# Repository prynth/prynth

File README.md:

# Prynth
The Prynth framework uses the Raspberry Pi (RPi) for sound synthesis and the Teensy microcontroller for sensor signal acquisition. The Teensy communicates with the RPi through an add-on board, which in turn connects to up to 10 multiplexer boards for a total 80 analog sensor connections (pots, resistors or switches). It also includes connections for digital sensors through I2C and SPI buses.

With the Prynth framework, the RPi boots into a system that automatically runs a web service with a full code editor for the SuperCollider programing language.

For more information please visit the [Prynth website](https://prynth.github.io/).

# Installation

## Prepare the OS

- Flash the latest Raspbian Lite image (https://www.raspberrypi.org/software/operating-systems/#raspberry-pi-os-32-bit) to your microSD card.
- Mount the card on your computer and create an file named ssh located at the root of the boot folder. In Linux:\
`
touch ssh
`
- If you want connect straight to your WiFi, you can also create a wpa_supplicant.conf file on the same booh folder. The wpa_supplicant.conf file should contain:
```
ctrl_interface=DIR=/var/run/wpa_supplicant GROUP=netdev
update_config=1
country=GB
network={
    ssid="your_real_wifi_ssid"
    scan_ssid=1
    psk="your_real_password"
    key_mgmt=WPA-PSK
}
```
- Boot Raspberry Pi.

## Expand filesystem
- SSH to Raspberry Pi and run the Raspbian configuration program.
  - `sudo raspi-config`
- Expand filesystem: "7 Advanced Options" > "A1 Expand Filesystem".
- Reboot.

## Upgrade and install additional libraries
- SSH to Raspberry Pi.
- Update libraries.
  - `sudo apt-get update`
  - `sudo apt-get upgrade`
  - `sudo apt-get dist-upgrade`

- Install additional libraries required for Jack and SuperCollider.
- `sudo apt-get install libsamplerate0-dev libsndfile1-dev libasound2-dev libavahi-client-dev libreadline-dev libfftw3-dev libudev-dev libncurses5-dev cmake git`
- Reboot.

## Compile and install Jack
- `git clone git://github.com/jackaudio/jack2 --depth 1`
- `cd jack2`
- `./waf configure --alsa --libdir=/usr/lib/arm-linux-gnueabihf/`
- `./waf build`
- `sudo ./waf install`
- `sudo ldconfig`
- `cd .. && rm -rf jack2`

## Set limits.conf
- `sudo sh -c "echo @audio - memlock 256000 >> /etc/security/limits.conf"`
- `sudo sh -c "echo @audio - rtprio 75 >> /etc/security/limits.conf"`
- `exit # and ssh in again to make the limits.conf settings work`

## Compile and install Supercollider
- `git clone --recurse-submodules https://github.com/supercollider/supercollider.git`
- `cd supercollider`
- `mkdir build && cd build`
- `cmake -DCMAKE_BUILD_TYPE=Release -DSUPERNOVA=OFF -DSC_ED=OFF -DSC_EL=OFF -DSC_VIM=ON -DNATIVE=ON -DSC_IDE=OFF -DNO_X11=ON -DSC_QT=OFF ..`
- `sudo cmake --build . --config Release --target install`
- `sudo ldconfig`

## Test Jack and SuperCollider
- Connect your soundcard (USB or I2S)
- Run Jack with sound device 1 (-dhw:1)
  - `jackd -P75 -dalsa -dhw:1 -p1024 -n3 -s -r44100 &`
- Run SuperCollider
  - `sclang`
- Inside the sclang shell, boot the server and play an event. You should hear a sound.
  - `s.boot`
  - `(dur:3).play`
- Quit the server and exit sclang
  - `s.quit`
  - `0.exit`

## Setup UART for Prynth boards and enable overclocking
- SSH to Raspberry Pi.
- Run Raspiconfig:
  - `sudo raspi-config`
- Disable shell over serial and enable hardware port:
  - 5 Interfacing Options > P6 Serial
  - "Would you like a login shell to be accessible over serial?" > No
  - "Would you like the serial port hardware to be enabled?" > Yes
- Reboot.
- SSH to Raspberry Pi.
- Additional boot settings (disable Bluetooth and enable overclocking)
  - `sudo sh -c "echo dtoverlay=pi3-disable-bt >> /boot/config.txt"`
## Clone prynth in the pi home folder
- `cd ~`
- `git clone https://github.com/prynth/prynth.git`  

## Install Node.js, liblo and WiringPi
- `sudo apt-get install nodejs liblo7 liblo-dev wiringpi`

## Recompile the pbridge application
- `gcc -o /home/pi/prynth/pbridge/pbridge /home/pi/prynth/pbridge/src/pbridge.c -lwiringPi -llo`

## Enable Prynth at startup
- Launch crontab
  - `crontab -e`
- Choose your preferred text editor (nano is easier)
- Add the following line at the end of the file:
  - `@reboot sudo nodejs /home/pi/prynth/server/bin/www`
- Reboot.

# Notes
For more information please refer to the [Prynth documentation](https://prynth.github.io/doc/). Prynth is also distributed as a ready-to-use image file hosted on the [Downloads](https://prynth.github.io/create/downloads.html) section.

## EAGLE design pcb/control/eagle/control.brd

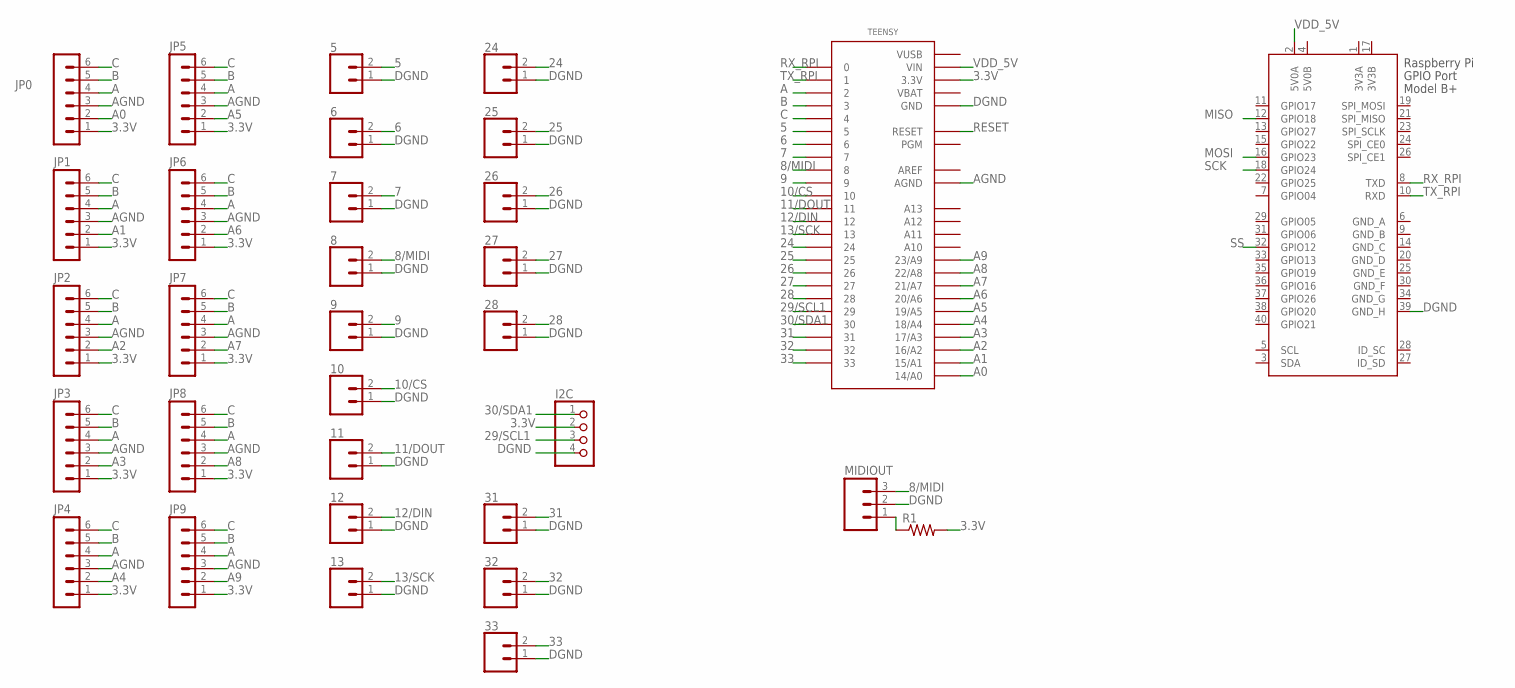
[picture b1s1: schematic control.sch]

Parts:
5, 6, 7, 8, 9, 10, 11, 12, 13, 24, 25, 26, 27, 28, 31, 32, 33: CONN_02; 1X02
I2C: PINHD-1X4; 1X04
JP0, JP1, JP2, JP3, JP4, JP5, JP6, JP7, JP8, JP9: MA06-1
MIDIOUT: M03PTH; 1X03
R1: RESISTORAXIAL-0.3; AXIAL-0.3
TEENSY: TEENSY_3.0_ALLPINS
X1: RASPI_BOARD_B+#_H; RASPI_BOARD_B+HAT

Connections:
3.3V: I2C.2, JP0.1, JP1.1, JP2.1, JP3.1, JP4.1, JP5.1, JP6.1, JP7.1, JP8.1, JP9.1, R1.P$2 (2), TEENSY.3.3V, TEENSY.3.3V1 (3.3V), TEENSY.3.3V2 (3.3V)
3V3A: X1.1 (3V3A)
3V3B: X1.17 (3V3B)
5: 5.2, TEENSY.5
5V0B: X1.4 (5V0B)
6: 6.2, TEENSY.6
7: 7.2, TEENSY.7
8/MIDI: 8.2, MIDIOUT.3, TEENSY.8
9: 9.2, TEENSY.9
10/CS: 10.2, TEENSY.10
11/DOUT: 11.2, TEENSY.11
12/DIN: 12.2, TEENSY.12
13/SCK: 13.2, TEENSY.13
24: 24.2, TEENSY.24
25: 25.2, TEENSY.25
26: 26.2, TEENSY.26
27: 27.2, TEENSY.27
28: 28.2, TEENSY.28
29/SCL1: I2C.3, TEENSY.29
30/SDA1: I2C.1, TEENSY.30
31: 31.2, TEENSY.31
32: 32.2, TEENSY.32
33: 33.2, TEENSY.33
A: JP0.4, JP1.4, JP2.4, JP3.4, JP4.4, JP5.4, JP6.4, JP7.4, JP8.4, JP9.4, TEENSY.2
A0: JP0.2, TEENSY.14/A0
A1: JP1.2, TEENSY.15/A1
A2: JP2.2, TEENSY.16/A2
A3: JP3.2, TEENSY.17/A3
A4: JP4.2, TEENSY.18/A4
A5: JP5.2, TEENSY.19/A5
A6: JP6.2, TEENSY.20/A6
A7: JP7.2, TEENSY.21/A7
A8: JP8.2, TEENSY.22/A8
A9: JP9.2, TEENSY.23/A9
AGND: JP0.3, JP1.3, JP2.3, JP3.3, JP4.3, JP5.3, JP6.3, JP7.3, JP8.3, JP9.3, TEENSY.AGND
AREF: TEENSY.AREF
B: JP0.5, JP1.5, JP2.5, JP3.5, JP4.5, JP5.5, JP6.5, JP7.5, JP8.5, JP9.5, TEENSY.3
C: JP0.6, JP1.6, JP2.6, JP3.6, JP4.6, JP5.6, JP6.6, JP7.6, JP8.6, JP9.6, TEENSY.4
DGND: 5.1, 6.1, 7.1, 8.1, 9.1, 10.1, 11.1, 12.1, 13.1, 24.1, 25.1, 26.1, 27.1, 28.1, 31.1, 32.1, 33.1, I2C.4, MIDIOUT.2, TEENSY.GND, TEENSY.GND1 (GND), TEENSY.GND2 (GND), X1.39 (GND_H)
GND_A: X1.6 (GND_A)
GND_B: X1.9 (GND_B)
GND_C: X1.14 (GND_C)
GND_D: X1.20 (GND_D)
GND_E: X1.25 (GND_E)
GND_F: X1.30 (GND_F)
GND_G: X1.34 (GND_G)
MISO: X1.12 (GPIO18)
MOSI: X1.16 (GPIO23)
unnamed: MIDIOUT.1, R1.P$1 (1)
RESET: TEENSY.RESET
RX_RPI: TEENSY.0, X1.8 (TXD)
SCK: X1.18 (GPIO24)
SS: X1.32 (GPIO12)
TX_RPI: TEENSY.1, X1.10 (RXD)
VBAT: TEENSY.VBAT
VDD_5V: TEENSY.VIN, X1.2 (5V0A)
VUSB: TEENSY.VUSB

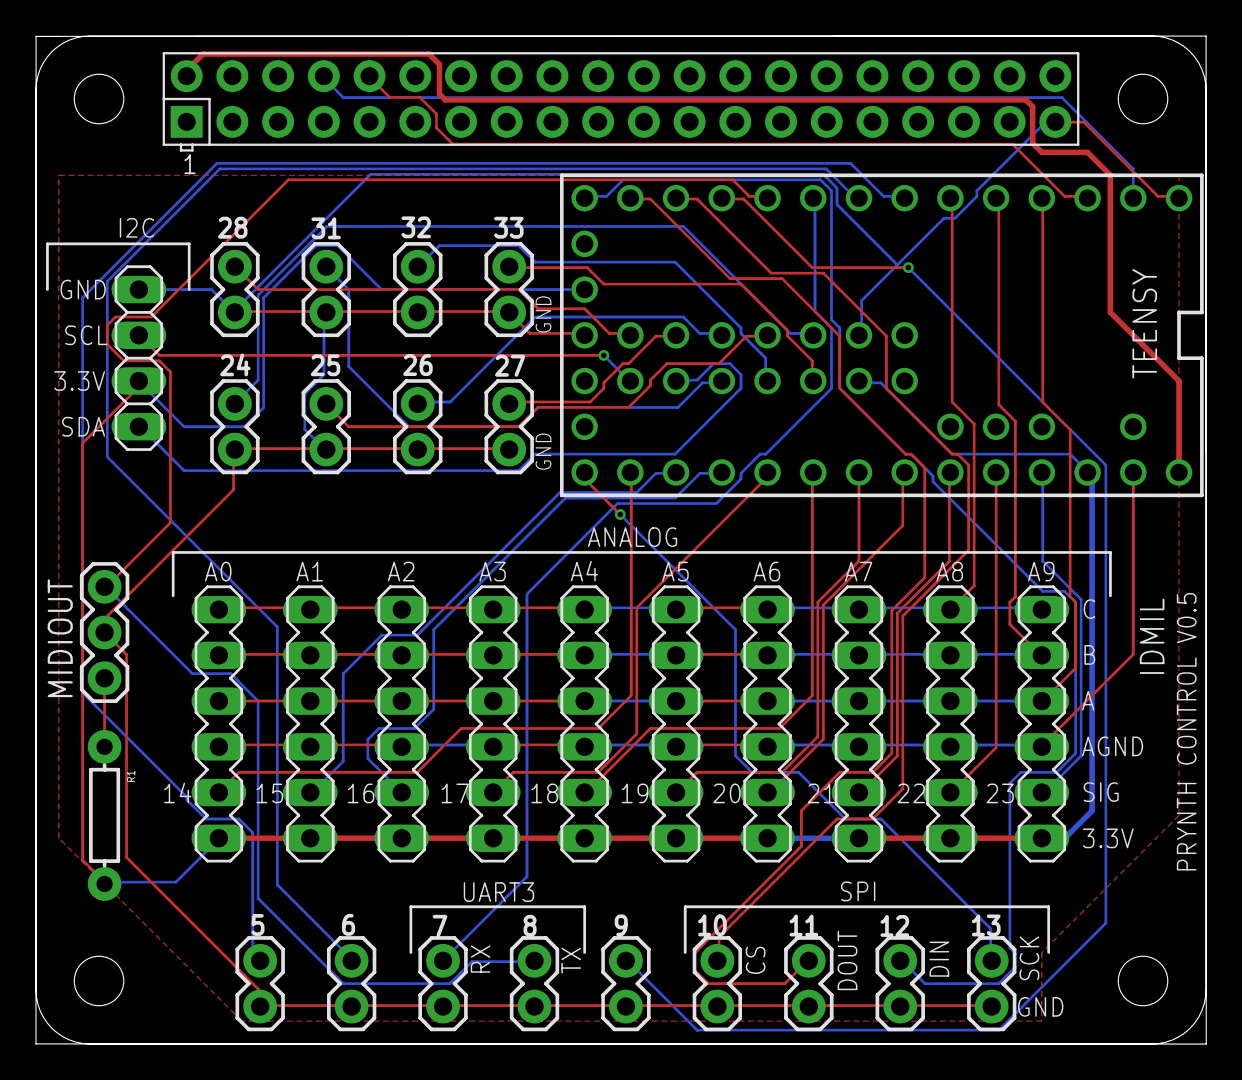
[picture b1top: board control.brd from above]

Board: 2 copper layers, 65.0 x 56.0 mm, 32 parts (0 on the bottom side), 39 nets.

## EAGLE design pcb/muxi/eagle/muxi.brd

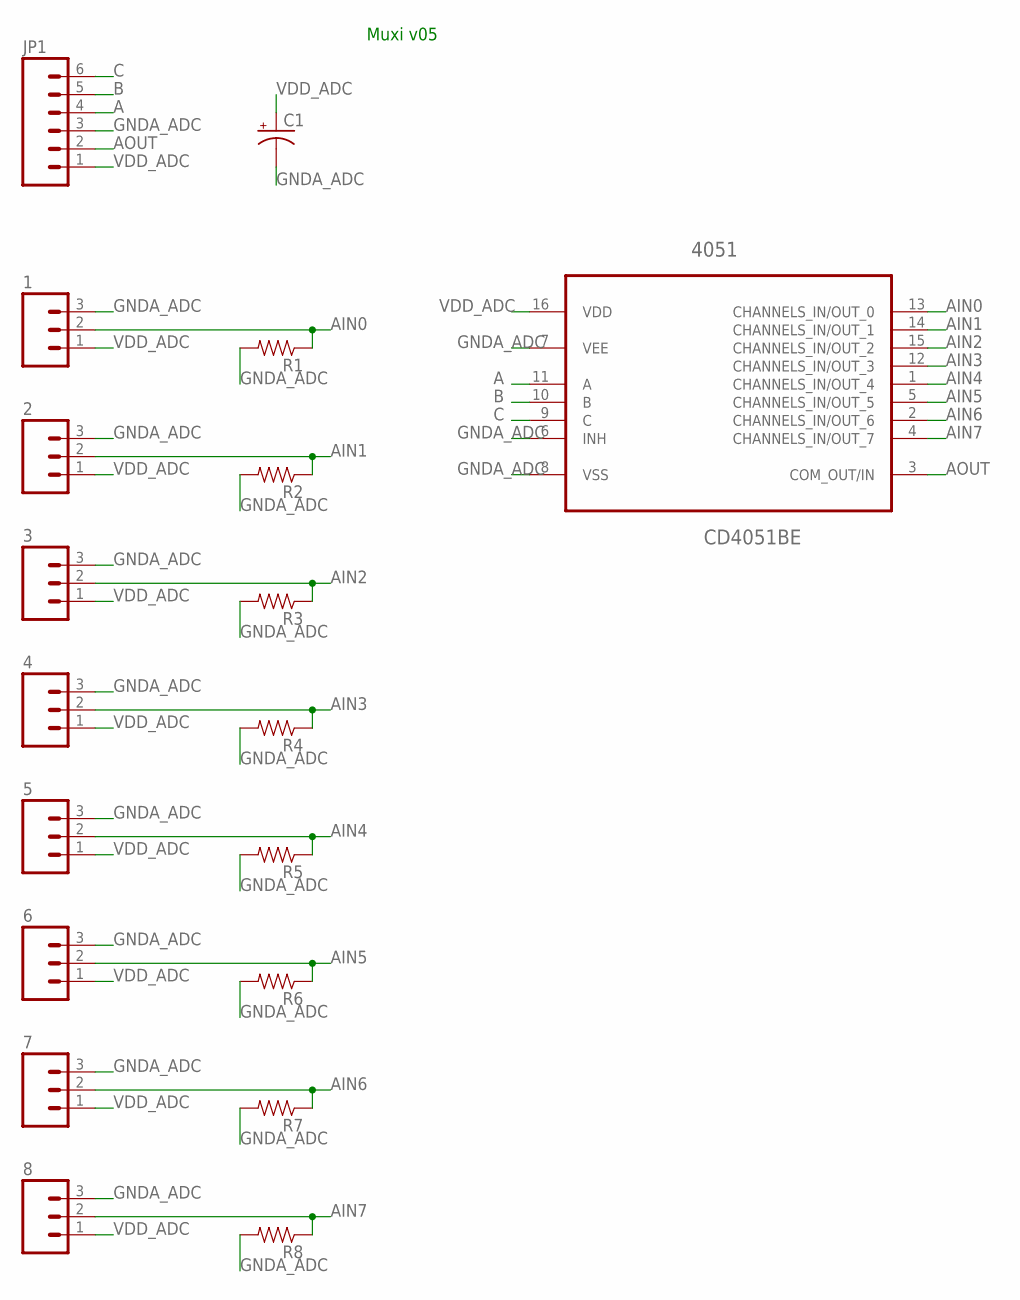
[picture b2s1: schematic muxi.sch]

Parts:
1, 2, 3, 4, 5, 6, 7, 8: M03PTH; 1X03
4051: CD4051BE; DIP254P762X508-16
C1: CAP_POLPTH2; CPOL-RADIAL-10UF-25V
JP1: M06NO_SILK; 1X06_NO_SILK
R1, R2, R3, R4, R5, R6, R7, R8: RESISTORAXIAL-0.3; AXIAL-0.3

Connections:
A: 4051.11 (A), JP1.4
AIN0: 1.2, 4051.13 (CHANNELS_IN/OUT_0), R1.P$1 (1)
AIN1: 2.2, 4051.14 (CHANNELS_IN/OUT_1), R2.P$1 (1)
AIN2: 3.2, 4051.15 (CHANNELS_IN/OUT_2), R3.P$1 (1)
AIN3: 4.2, 4051.12 (CHANNELS_IN/OUT_3), R4.P$1 (1)
AIN4: 5.2, 4051.1 (CHANNELS_IN/OUT_4), R5.P$1 (1)
AIN5: 6.2, 4051.5 (CHANNELS_IN/OUT_5), R6.P$1 (1)
AIN6: 7.2, 4051.2 (CHANNELS_IN/OUT_6), R7.P$1 (1)
AIN7: 8.2, 4051.4 (CHANNELS_IN/OUT_7), R8.P$1 (1)
AOUT: 4051.3 (COM_OUT/IN), JP1.2
B: 4051.10 (B), JP1.5
C: 4051.9 (C), JP1.6
GNDA_ADC: 1.3, 2.3, 3.3, 4.3, 5.3, 6.3, 7.3, 8.3, 4051.6 (INH), 4051.7 (VEE), 4051.8 (VSS), C1.2 (-), JP1.3, R1.P$2 (2), R2.P$2 (2), R3.P$2 (2), R4.P$2 (2), R5.P$2 (2), R6.P$2 (2), R7.P$2 (2), R8.P$2 (2)
VDD_ADC: 1.1, 2.1, 3.1, 4.1, 5.1, 6.1, 7.1, 8.1, 4051.16 (VDD), C1.1 (+), JP1.1

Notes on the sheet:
Muxi v05

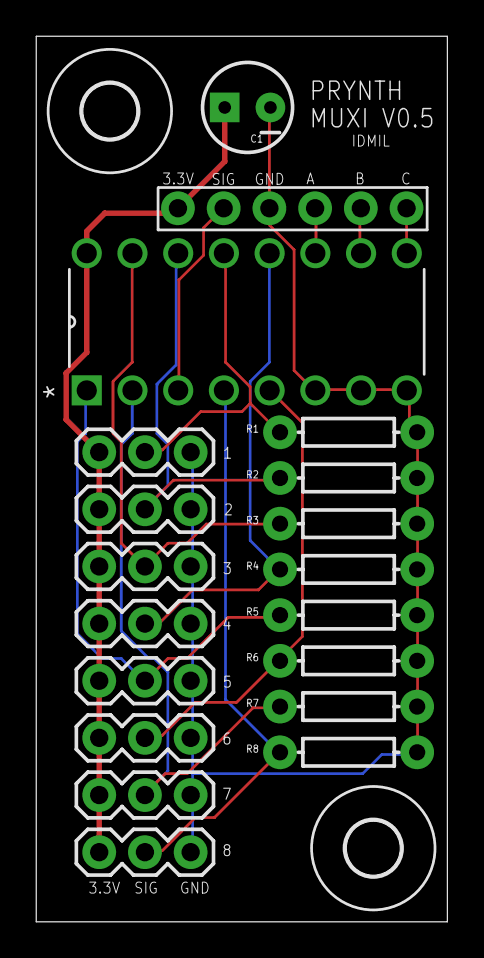
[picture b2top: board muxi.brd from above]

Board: 2 copper layers, 22.8 x 49.2 mm, 21 parts (0 on the bottom side), 14 nets.

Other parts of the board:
U$1, U$2: 3,0

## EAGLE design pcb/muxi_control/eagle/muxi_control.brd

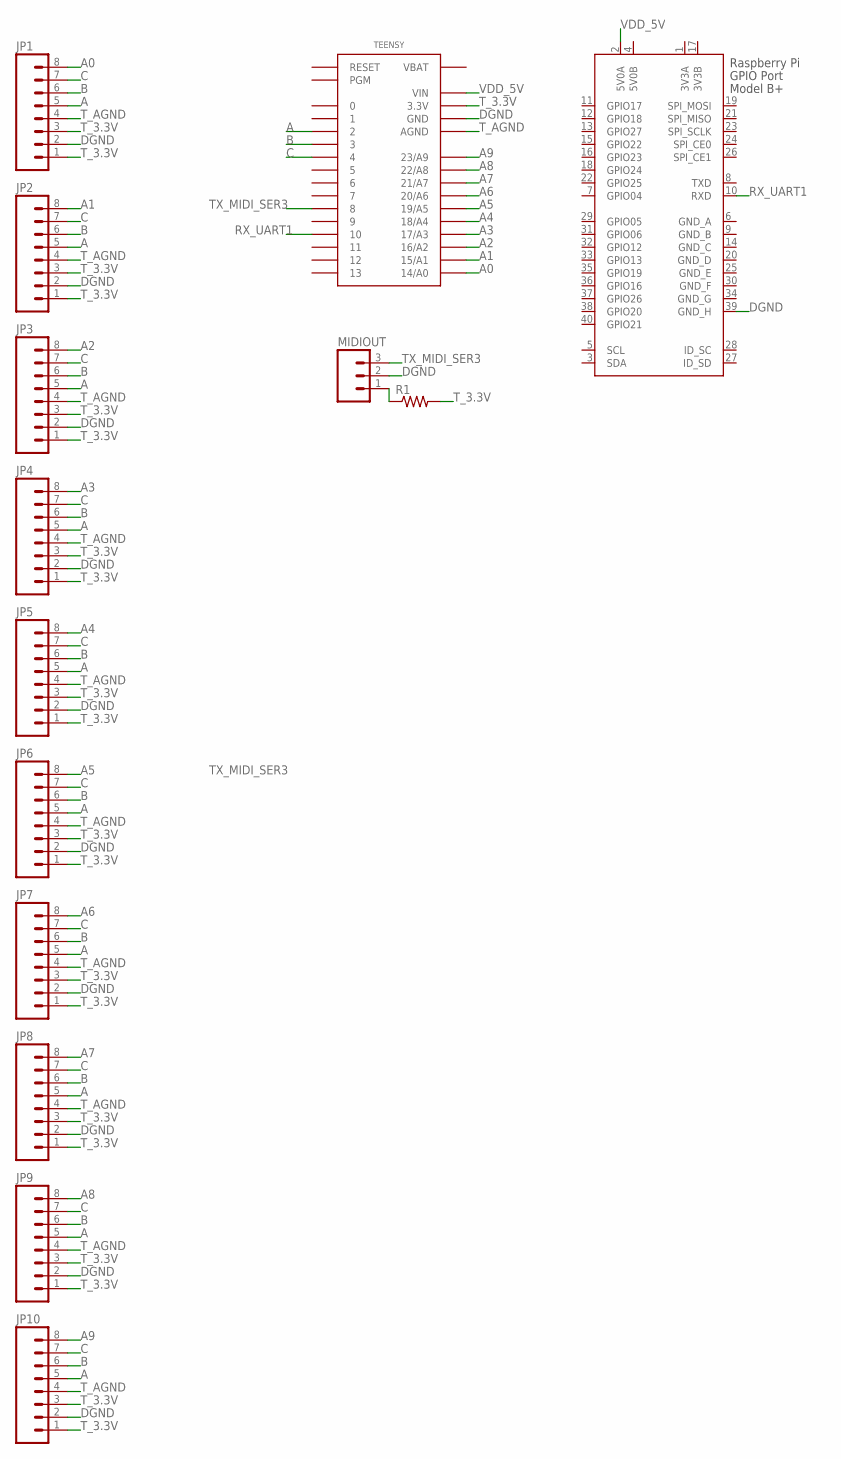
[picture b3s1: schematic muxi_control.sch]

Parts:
JP1, JP2, JP3, JP4, JP5, JP6, JP7, JP8, JP9, JP10: M081X08; 1X08
MIDIOUT: M03PTH; 1X03
R1: RESISTORAXIAL-0.3; AXIAL-0.3
TEENSY: TEENSY_3.0_BASIC
X1: RASPI_BOARD_B+#_H; RASPI_BOARD_B+HAT

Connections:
3V3A: X1.1 (3V3A)
3V3B: X1.17 (3V3B)
5V0B: X1.4 (5V0B)
A: JP1.5, JP2.5, JP3.5, JP4.5, JP5.5, JP6.5, JP7.5, JP8.5, JP9.5, JP10.5, TEENSY.2
A0: JP1.8, TEENSY.14/A0
A1: JP2.8, TEENSY.15/A1
A2: JP3.8, TEENSY.16/A2
A3: JP4.8, TEENSY.17/A3
A4: JP5.8, TEENSY.18/A4
A5: JP6.8, TEENSY.19/A5
A6: JP7.8, TEENSY.20/A6
A7: JP8.8, TEENSY.21/A7
A8: JP9.8, TEENSY.22/A8
A9: JP10.8, TEENSY.23/A9
B: JP1.6, JP2.6, JP3.6, JP4.6, JP5.6, JP6.6, JP7.6, JP8.6, JP9.6, JP10.6, TEENSY.3
C: JP1.7, JP2.7, JP3.7, JP4.7, JP5.7, JP6.7, JP7.7, JP8.7, JP9.7, JP10.7, TEENSY.4
DGND: JP1.2, JP2.2, JP3.2, JP4.2, JP5.2, JP6.2, JP7.2, JP8.2, JP9.2, JP10.2, MIDIOUT.2, TEENSY.GND, TEENSY.GND1 (GND), X1.39 (GND_H)
GND_A: X1.6 (GND_A)
GND_B: X1.9 (GND_B)
GND_C: X1.14 (GND_C)
GND_D: X1.20 (GND_D)
GND_E: X1.25 (GND_E)
GND_F: X1.30 (GND_F)
GND_G: X1.34 (GND_G)
unnamed: MIDIOUT.1, R1.P$1 (1)
RX_UART1: TEENSY.10, X1.10 (RXD)
TX_MIDI_SER3: MIDIOUT.3, TEENSY.8
T_3.3V: JP1.1, JP1.3, JP2.1, JP2.3, JP3.1, JP3.3, JP4.1, JP4.3, JP5.1, JP5.3, JP6.1, JP6.3, JP7.1, JP7.3, JP8.1, JP8.3, JP9.1, JP9.3, JP10.1, JP10.3, R1.P$2 (2), TEENSY.3.3V, TEENSY.3.3V1 (3.3V)
T_AGND: JP1.4, JP2.4, JP3.4, JP4.4, JP5.4, JP6.4, JP7.4, JP8.4, JP9.4, JP10.4, TEENSY.AGND
VBAT: TEENSY.VBAT
VDD_5V: TEENSY.VIN, X1.2 (5V0A)

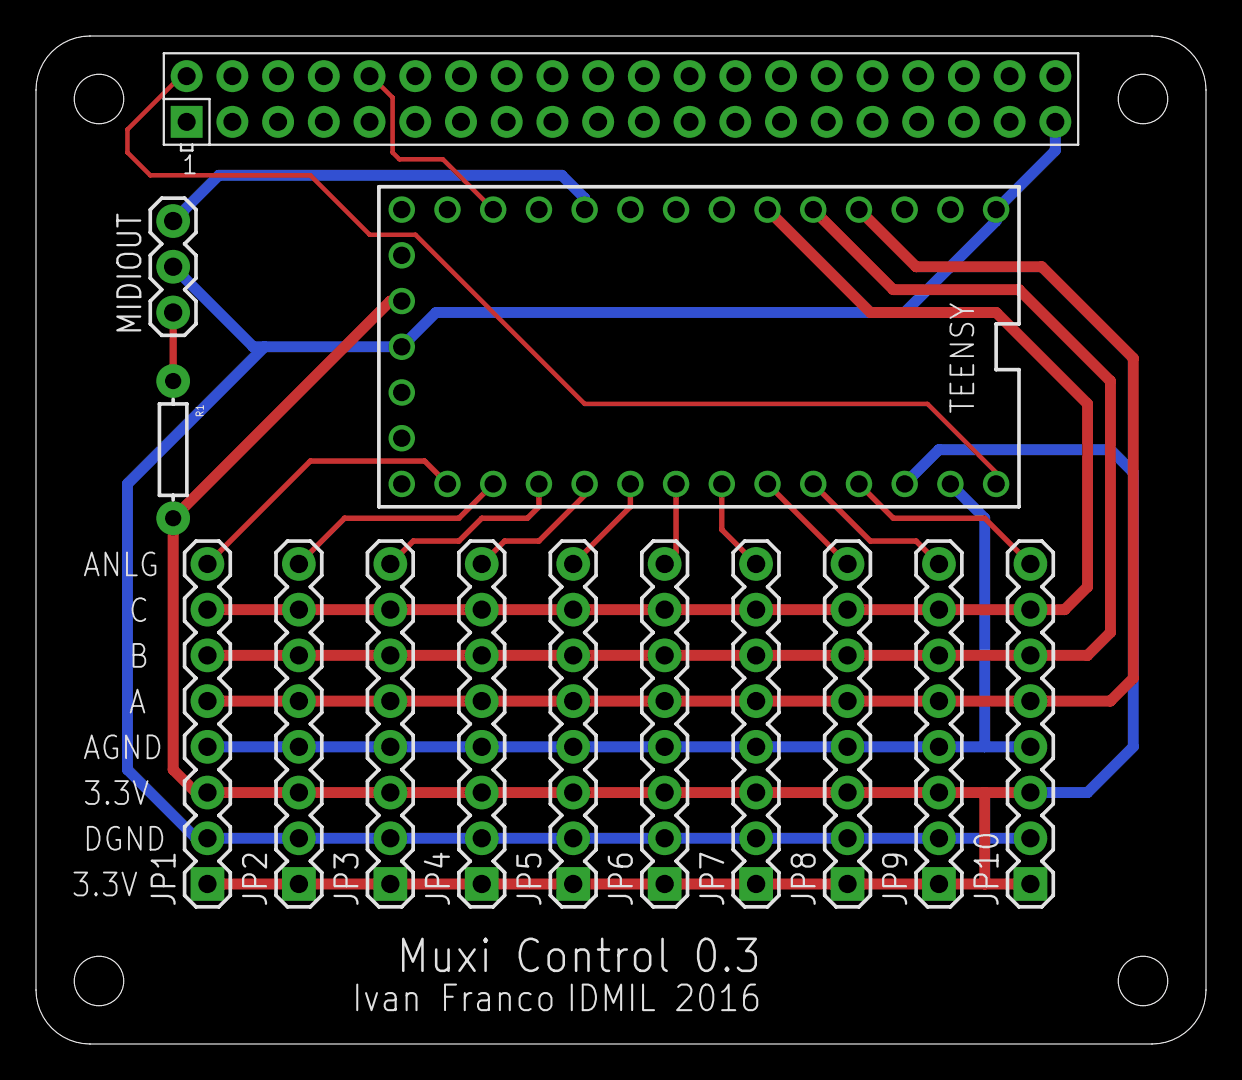
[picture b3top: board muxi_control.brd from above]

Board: 2 copper layers, 65.0 x 56.0 mm, 14 parts (0 on the bottom side), 20 nets.

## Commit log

2016-11-09 scripts updated to new paths
2016-11-09 serial2osc and examples file cleanup
2016-11-10 updates to server main page
2016-11-10 cleaned server frontpage
2016-11-10 idea project file update
2016-12-05 change default filtering settings on teensy code
2016-12-13 updated gerbers
2016-12-14 changed teensy filtering and comments
2017-08-02 modified gitignore
2017-08-02 new v04 server version
2017-08-02 added serial2osc and teensy folders
2017-08-02 fixed relative path config.json
2017-08-02 fixed help path
2017-08-03 updated gitignore
2017-08-07 changes in settings. Config files edited via sed
2017-08-07 changed path in sed command for wpa
2017-08-07 changed key in sed command
2017-08-07 change things in sed command
2017-08-07 changed password type in wpa
2017-08-07 implemented hostname pull in settings
2017-08-07 changed typo in settings
2017-08-07 added reboot and shutdown to settings page
2017-08-07 fixed bug in reboot and shutdown settings
2017-08-07 added hostname editing
2017-08-08 start jack from node app
2017-08-08 start serial2osc from node app
2017-08-08 changed code examples
2017-08-08 reverted back to crontab-based startup
2017-08-09 back to apps lauched via server
2017-08-09 experimenting with child processes for launching side apps
2017-08-09 change sensor data target between language and server via prynth frontend
2017-08-09 change jack settings via prynth frontend
2017-08-11 changed serial2osc generated path to relative path
2017-08-17 changed serial2osc data structure to language so that sensor reference is included in path together with hostname
2017-08-17 added compiled serial2osc
2017-08-17 new osc to language example
2017-08-18 implemented jack options on Settings
2017-08-18 moved sclang initialization to jack initialization callback function
2017-08-18 reverted sclang initialization
2017-08-18 restored jack process initialization from node with fallback on jackd.rc
2017-08-22 restructured application directories
2017-08-22 removed scd examples
2017-08-23 added hidden file filtering in file management
2017-08-23 added temp file run system for big strings
2017-08-23 persistent code buffer for refreshing purposes
2017-08-23 changed file refresh functions
2017-08-23 fixed temp file handling
2017-08-24 added elastic web properties to editor page
2017-08-24 fixed html margins
2017-08-25 changed system info panel back to main page. Removed heart. Changed nomenclature settings to system
2017-08-25 added function and button to restart sclang
2017-08-25 changed nomenclature of button to restart sclang
2017-08-25 added commenting to codemirror
2017-08-27 fixed reboot and shutdown.
2017-08-28 added timeout for first sclang initialization
2017-08-28 fixed editor managers div anchoring
2017-08-30 fixed settings to system paths
2017-08-30 added option of 128 for vector size
2017-08-30 serial source code didn't correspond to binary version
2017-08-30 fixed serial 2 language example
2017-08-31 changed restartSclang function to include restarting serial2osc and jack
2017-08-31 switched positions of system and restart sc buttons
2017-08-31 changed restartSclang (callbacks)
2017-09-05 48 sample rate default
2017-09-05 added P95 priority to jack
2017-09-05 changed shutdown function
2017-09-11 added forced USB 1.1 mode
2017-09-11 cleanup soundfiles
2017-09-11 touched up default config.json
2017-09-12 removed vector 64 option
2017-09-21 added check existance of default file
2018-02-12 execute block enclosed in parenthesis, search current word, auto-populate save dialog, textarea overload fix, codemirror highlight and execute block
2018-02-12 Update serial2osc.c
    Fixed digital value inversion bug.
2018-02-12 test foo.txt added
2018-02-12 testing conflict
2018-02-12 Add files via upload
    new serial2osc binary (fixed digital data inversion)
2018-02-12 more testing thingies
2018-02-13 search autopopulate feature
2018-02-13 fake commit
2018-02-13 try to merge with abcdef
2018-02-13 merging fiasfad with please work
2018-02-13 local changes
2018-02-20 recompiled serial2osc
2018-02-20 teensy legacy and new v04 have their own folders; increased default frequency on prynth_v04.ino
2018-02-20 set default sampling rate to 44100 and usb 1.1 force to false
2018-02-26 abstracted run selected text function
2018-02-26 cleaned index.ejs
2018-02-26 updated nodejs modules
2018-02-26 cleaned event on help search
2018-02-27 fixed error verbosity; increase console output size limits
2018-02-27 fixed command.period behaviour
2018-03-01 fixed error where verbosity was still showing all executed code when ran via temp file
2018-03-02 commented unneeded console.log
2018-03-02 added option to resize console textarea
2018-03-03 implemented new method to set wifi via wpa_cli
2018-03-03 removed alert from network settings submit
2018-03-03 added commands to down and up wlan0 after setting network
2018-03-03 added reboot confirmation prompt in some of the settings save buttons
2018-03-03 restored timeout between jack and sc
2018-03-03 added callback mechanism to start sclang after jack
2018-03-04 added mode for sc classes
2018-03-09 removed foo.txt
2018-03-16 added favicon
2018-03-16 fixed some css error dealing with *selected*
2018-03-17 deleted .idea config files on project root
2018-03-27 fixed socket io map issue
2018-05-19 restored pcb boards zip file
2018-05-30 updated codemirror version
2018-05-30 deleted old muxi_control folder
2018-05-30 added teensy source code zip for inernet distribution
2018-05-31 added anchors to documentation
2018-05-31 changed images resolution on documentation
2018-05-31 Schmitt spelling
2018-06-01 added gui functions
2018-06-01 re-enabled jack
2018-06-01 added foo.json to guifiles
2018-06-01 fixed button behaviour from impulse to button
2018-06-06 renabled sclang error handling
2018-06-08 fixed problem with saving sensors wouldn't reload sensors.json
2018-06-08 reset of sensors.json
2018-07-18 added new compressed muxi files
2018-08-29 substituted old mode switch by a Nexus object
2018-10-17 sync with master, gui introduction, fixed CPU statistics
2018-10-17 Schmidt trigger selection now hides unused slider controls
2018-10-17 GUI OSC messages preceded by hostname, modules update
2018-10-18 clean up of gui code
2018-10-18 automatic loading of last saved GUI
2018-10-19 autoload last saved gui file
2018-10-19 fixed floating point values of gui elements now rounded to two decimal places
2018-10-19 code improvements
2018-10-19 gui.ejs code clean up
2018-10-19 changed slider and knob resolution; more code cleanup
2018-10-19 added gui example
2018-10-22 added Nexus UI number object
2018-10-22 added Nexus number to gui, reduced button default size
2018-10-22 changed Nexus number box default size
2018-10-22 added position object test
2018-10-22 added gui button to index; removed Nexus Position test
2018-10-22 gui fine tunnings
2018-10-26 GUI gui fine-tuning; example gui fine-tuning
2018-10-26 documentation editing to include GUIs
2018-10-29 added GUI help; updated supercollider help documentation; search string from shortcut is now broken
2018-10-29 search class from editor now works again
2018-10-29 added option of vector size 64
2018-10-30 rendered last prynth help markdown to html
2018-10-30 added option in settings for number of periods; fixed sc help launch from editor button
2018-10-30 documentation update, including screenshot images
2019-09-09 updated npm packages
2019-09-09 fixed font size of HTML select and dropdowns
2019-11-19 Created README file
2020-12-27 added README
2020-12-30 fixed teensy code for new arduino (1.8.13)and teensy library (1.53)
2020-12-30 updated README and compressed new teensy code
2021-01-12 update of supercollider documentation on Prynth server
2021-01-12 update of prynth documentation
2021-01-12 update to index.html on prynth documentation for relative image paths
2021-01-20 Bump socket.io from 2.1.1 to 2.4.0 in /server
    Bumps [socket.io](https://github.com/socketio/socket.io) from 2.1.1 to 2.4.0.
    - [Release notes](https://github.com/socketio/socket.io/releases)
    - [Changelog](https://github.com/socketio/socket.io/blob/2.4.0/CHANGELOG.md)
    - [Commits](https://github.com/socketio/socket.io/compare/2.1.1...2.4.0)
2022-10-29 Bump socket.io-parser and socket.io in /server
    Bumps [socket.io-parser](https://github.com/socketio/socket.io-parser) to 3.3.2 and updates ancestor dependency [socket.io](https://github.com/socketio/socket.io). These dependencies need to be updat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
    Updates `socket.io-parser` from 3.1.2 to 3.3.2
    - [Release notes](https://github.com/socketio/socket.io-parser/releases)
    - [Changelog](https://github.com/socketio/socket.io-parser/blob/3.3.2/CHANGELOG.md)
    - [Commits](https://github.com/socketio/socket.io-parser/compare/3.1.2...3.3.2)
    Updates `socket.io` from 2.1.1 to 2.5.0
2022-11-10 Bump socket.io-parser and socket.io in /server
    Bumps [socket.io-parser](https://github.com/socketio/socket.io-parser) to 3.3.3 and updates ancestor dependency [socket.io](https://github.com/socketio/socket.io). These dependencies need to be updat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
    Updates `socket.io-parser` from 3.1.2 to 3.3.3
    - [Release notes](https://github.com/socketio/socket.io-parser/releases)
    - [Changelog](https://github.com/socketio/socket.io-parser/blob/main/CHANGELOG.md)
    - [Commits](https://github.com/socketio/socket.io-parser/compare/3.1.2...3.3.3)
    Updates `socket.io` from 2.1.1 to 2.5.0
2022-11-22 Bump engine.io and socket.io in /server
    Bumps [engine.io](https://github.com/socketio/engine.io) to 3.6.1 and updates ancestor dependency [socket.io](https://github.com/socketio/socket.io). These dependencies need to be updated together.
    Updates `engine.io` from 3.1.0 to 3.6.1
    - [Release notes](https://github.com/socketio/engine.io/releases)
    - [Changelog](https://github.com/socketio/engine.io/blob/main/CHANGELOG.md)
    - [Commits](https://github.com/socketio/engine.io/compare/3.1.0...3.6.1)
    Updates `socket.io` from 2.1.1 to 2.5.0
2022-12-07 Bump express from 4.16.2 to 4.17.3 in /server
    Bumps [express](https://github.com/expressjs/express) from 4.16.2 to 4.17.3.
    - [Release notes](https://github.com/expressjs/express/releases)
    - [Changelog](https://github.com/expressjs/express/blob/master/History.md)
    - [Commits](https://github.com/expressjs/express/compare/4.16.2...4.17.3)
    ---
    updated-dependencies:
2023-03-01 Bump minimist and mkdirp in /server
    Bumps [minimist](https://github.com/minimistjs/minimist) and [mkdirp](https://github.com/isaacs/node-mkdirp). These dependencies needed to be updated together.
    Updates `minimist` from 0.0.8 to 1.2.8
    - [Release notes](https://github.com/minimistjs/minimist/releases)
    - [Changelog](https://github.com/minimistjs/minimist/blob/main/CHANGELOG.md)
    - [Commits](https://github.com/minimistjs/minimist/compare/v0.0.8...v1.2.8)
    Updates `mkdirp` from 0.5.1 to 0.5.6

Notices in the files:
pcb/control/eagle/control.brd:
CC BY-SA 3.0
parts and their libraries:
SparkFun-Connectors: Licensing: Creative Commons ShareAlike 4.0 International - https://creativecommons.org/licenses/by-sa/4.0
